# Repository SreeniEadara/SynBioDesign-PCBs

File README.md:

# SynBioDesign-PCBs
Schematics and Layouts for PCBs students use in the Synthetic Biology Design intersession course

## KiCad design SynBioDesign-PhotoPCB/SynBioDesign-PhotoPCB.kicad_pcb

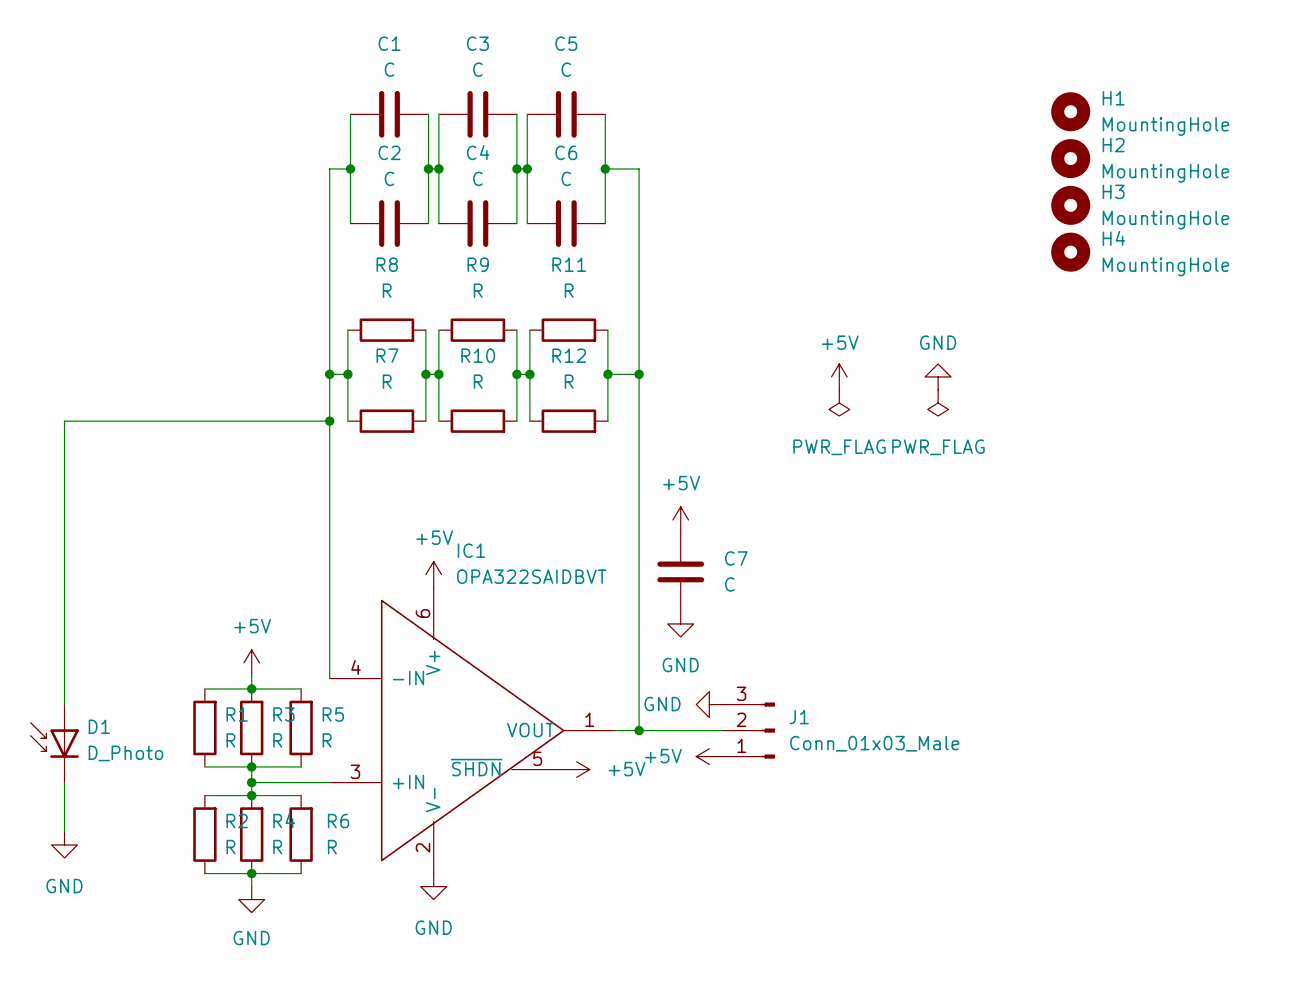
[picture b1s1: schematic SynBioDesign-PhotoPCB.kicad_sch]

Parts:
C1, C2, C3, C4, C5, C6, C7: C; C_Disc_D5.0mm_W2.5mm_P5.00mm
D1: D_Photo; LED_SFH2270R; DigiKey 475-3138-1-ND
H1, H2, H3, H4: MountingHole; MountingHole_3.2mm_M3_DIN965_Pad
IC1: OPA322SAIDBVT; SOT-23-6_Handsoldering; Manufacturer_Part_Number OPA322SAIDBVT; Mouser Part Number 595-OPA322SAIDBVT
J1: Conn_01x03_Male; PinHeader_1x03_P2.54mm_Vertical
R1, R2, R3, R4, R5, R6, R7, R8, R9, R10, R11, R12: R; R_Axial_DIN0204_L3.6mm_D1.6mm_P5.08mm_Horizontal

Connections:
+5V: C7.1, IC1.5 (~SHDN), IC1.6 (V+), J1.1, R1.2, R3.2, R5.2
GND: C7.2, D1.1 (K), IC1.2 (V-), J1.3, R2.1, R4.1, R6.1
unnamed: C1.1, C2.1, D1.2 (A), IC1.4 (-IN), R7.1, R8.1
unnamed: C1.2, C2.2, C3.1, C4.1
unnamed: C3.2, C4.2, C5.1, C6.1
unnamed: C5.2, C6.2, IC1.1 (VOUT), J1.2, R11.2, R12.2
unnamed: IC1.3 (+IN), R1.1, R2.2, R3.1, R4.2, R5.1, R6.2
unnamed: R7.2, R8.2, R9.1, R10.1
unnamed: R9.2, R10.2, R11.1, R12.1

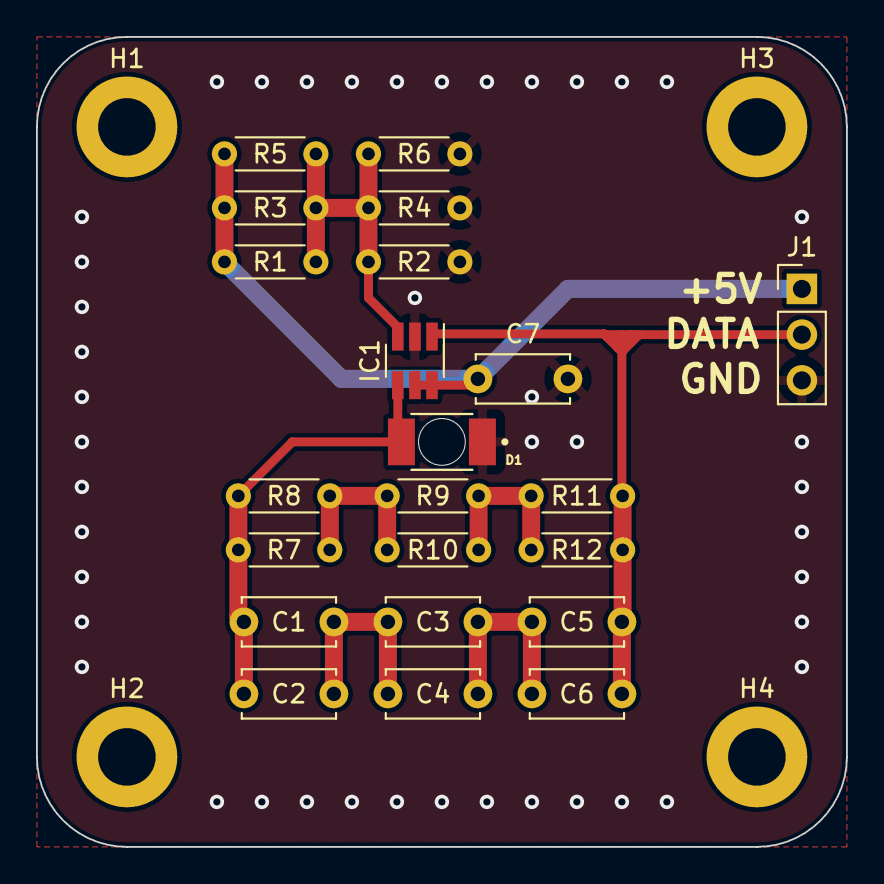
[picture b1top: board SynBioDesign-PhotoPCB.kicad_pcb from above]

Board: 2 copper layers, 45.0 x 45.0 mm, 26 parts (0 on the bottom side), 9 nets.

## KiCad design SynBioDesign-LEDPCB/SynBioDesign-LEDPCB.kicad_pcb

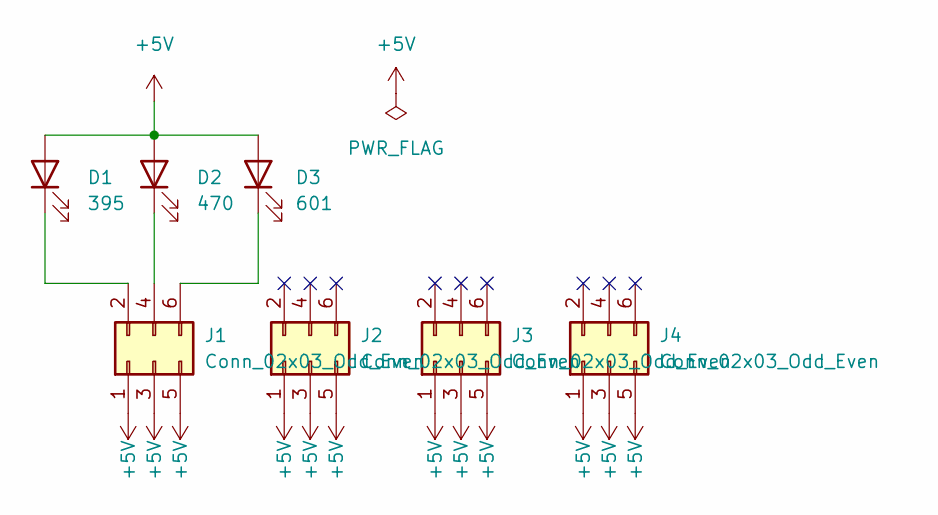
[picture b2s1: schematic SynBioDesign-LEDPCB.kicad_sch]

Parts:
D1: 395; LED_0805_2012Metric_Pad1.15x1.40mm_HandSolder; DigiKey 754-2319-1-ND
D2: 470; LED_0805_2012Metric_Pad1.15x1.40mm_HandSolder; DigiKey 754-1794-1-ND
D3: 601; LED_0805_2012Metric_Pad1.15x1.40mm_HandSolder; DigiKey 1497-1433-1-ND
J1, J2, J3, J4: Conn_02x03_Odd_Even; PinHeader_2x03_P2.54mm_Vertical

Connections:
+5V: D1.2 (A), D2.2 (A), D3.2 (A), J1.1, J1.3, J1.5, J2.1, J2.3, J2.5, J3.1, J3.3, J3.5, J4.1, J4.3, J4.5
unnamed: D1.1 (K), J1.2
unnamed: D2.1 (K), J1.4
unnamed: D3.1 (K), J1.6

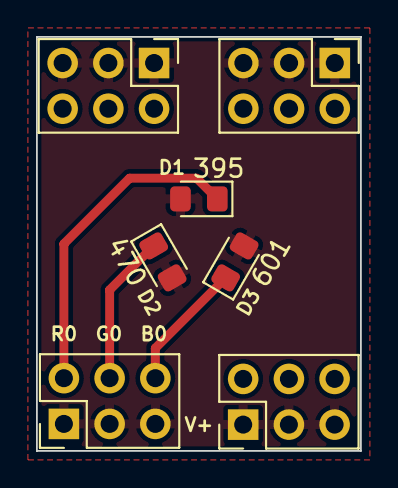
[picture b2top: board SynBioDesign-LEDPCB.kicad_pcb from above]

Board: 2 copper layers, 18.0 x 23.0 mm, 7 parts (0 on the bottom side), 4 nets.

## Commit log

2022-12-06 Adding PCB design files, initial revision
2022-12-06 Adding BOM csvs
2022-12-08 Adding silk
2022-12-08 Bug fixes
2022-12-08 Added pin label silk
2023-01-05 Adding 3D files for boards
